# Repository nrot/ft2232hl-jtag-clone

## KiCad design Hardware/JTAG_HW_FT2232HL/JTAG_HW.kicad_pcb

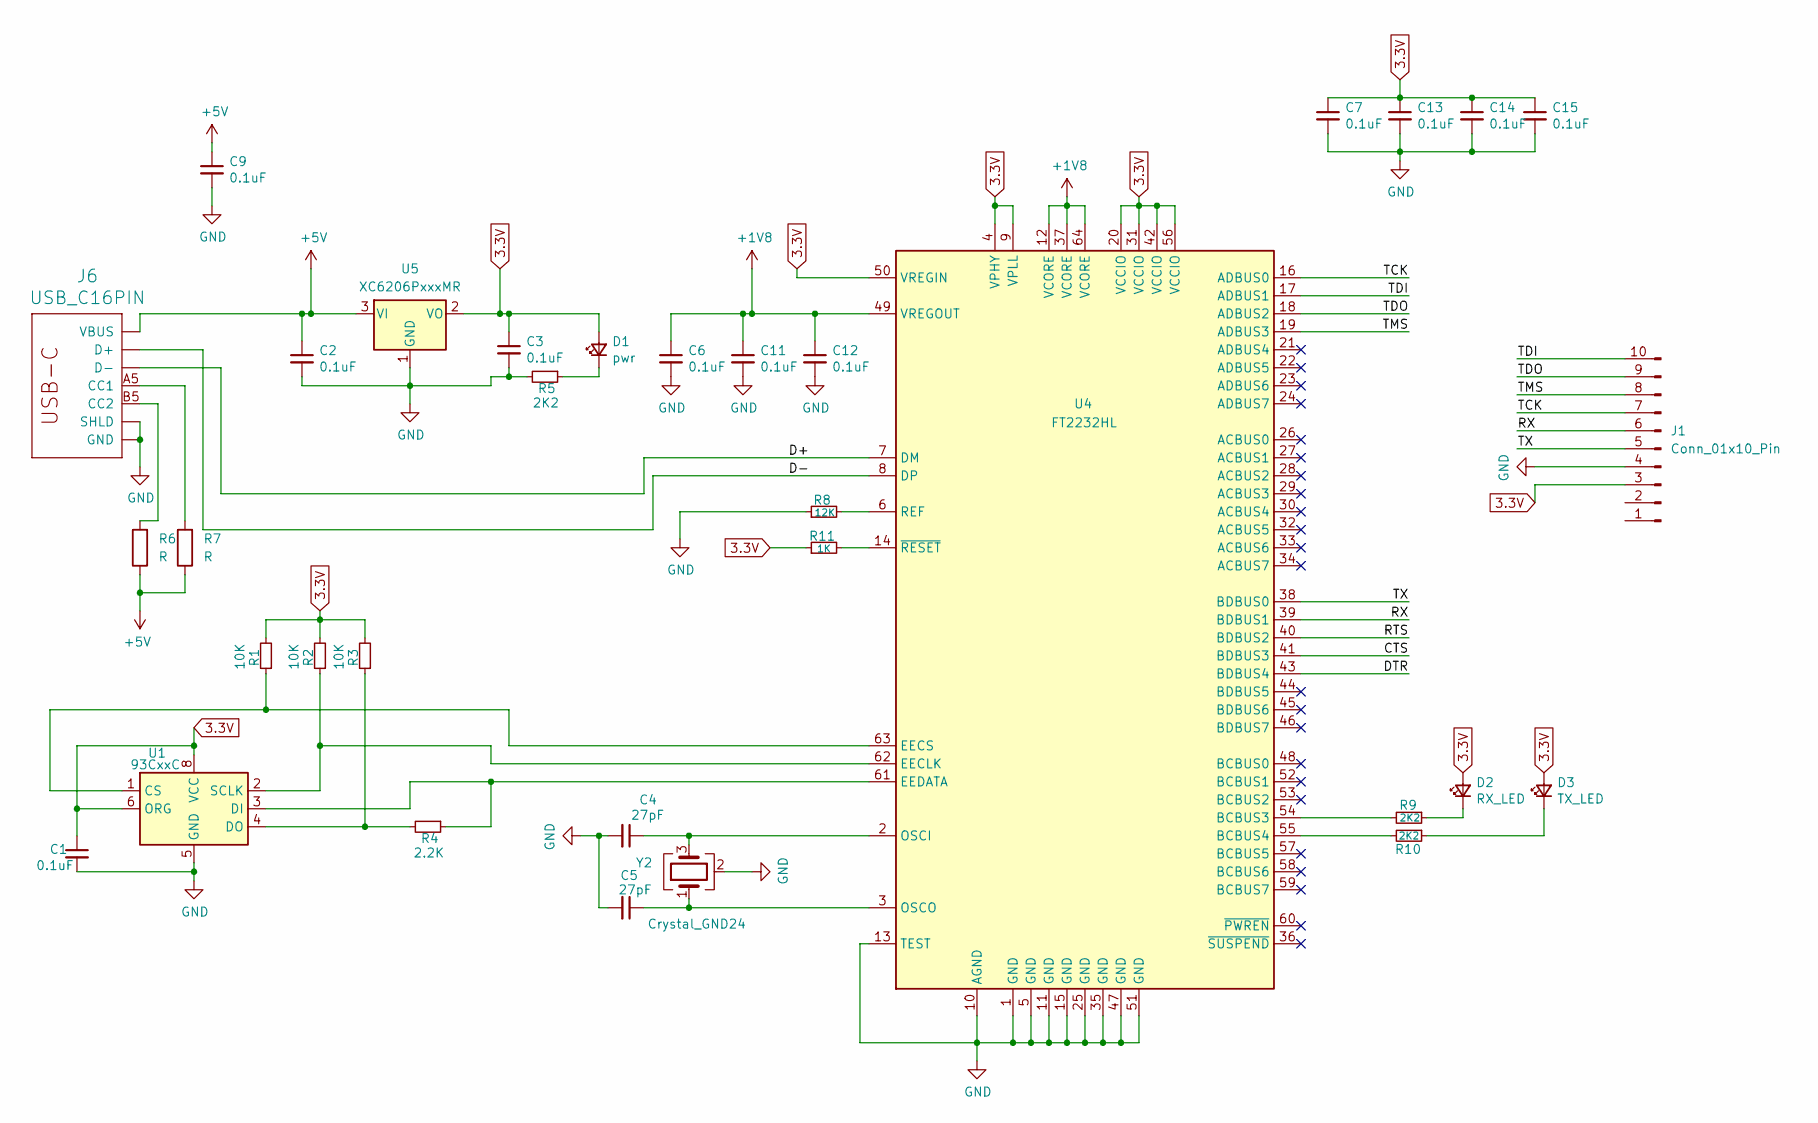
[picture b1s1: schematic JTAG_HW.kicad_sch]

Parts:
C1, C2, C3, C6, C7, C9, C11, C12, C13, C14, C15: 0.1uF; C_0805_2012Metric_Pad1.18x1.45mm_HandSolder
C4, C5: 27pF; C_0805_2012Metric_Pad1.18x1.45mm_HandSolder
D1: pwr; LED_0805_2012Metric_Pad1.15x1.40mm_HandSolder
D2: RX_LED; LED_0805_2012Metric_Pad1.15x1.40mm_HandSolder
D3: TX_LED; LED_0805_2012Metric_Pad1.15x1.40mm_HandSolder
J1: Conn_01x10_Pin; JST_SHL_SM10B-SHLS-TF_1x10-1MP_P1.00mm_Horizontal
J6: USB_C16PIN; USB-C-COM-15111
R1, R2, R3: 10K; R_0805_2012Metric_Pad1.20x1.40mm_HandSolder
R4: 2.2K; R_0805_2012Metric_Pad1.20x1.40mm_HandSolder
R5, R9, R10: 2K2; R_0805_2012Metric_Pad1.20x1.40mm_HandSolder
R6, R7: R
R8: 12K; R_0805_2012Metric_Pad1.20x1.40mm_HandSolder
R11: 1K; R_0805_2012Metric_Pad1.20x1.40mm_HandSolder
U1: 93CxxC; SOIC-8_3.9x4.9mm_P1.27mm
U4: FT2232HL; LQFP-64_10x10mm_P0.5mm
U5: XC6206PxxxMR; SOT-23-3
Y2: Crystal_GND24; Crystal_SMD_3225-4Pin_3.2x2.5mm_HandSoldering

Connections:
3.3V: C1.1, C3.1, C7.1, C13.1, C14.1, C15.1, D1.2 (A), D2.2 (A), D3.2 (A), J1.3, R1.2, R2.2, R3.2, R11.1, U1.6 (ORG), U1.8 (VCC), U4.4 (VPHY), U4.9 (VPLL), U4.20 (VCCIO), U4.31 (VCCIO), U4.42 (VCCIO), U4.50 (VREGIN), U4.56 (VCCIO), U5.2 (VO)
+1V8: C6.1, C11.1, C12.1, U4.12 (VCORE), U4.37 (VCORE), U4.49 (VREGOUT), U4.64 (VCORE)
+5V: C2.1, C9.1, J6.VBUS1 (VBUS), J6.VBUS2 (VBUS), R6.1, R7.1, U5.3 (VI)
/CTS: U4.41 (BDBUS3)
/D+: J6.A7 (D-), J6.B7 (D-), U4.7 (DM)
/D-: J6.A6 (D+), J6.B6 (D+), U4.8 (DP)
/DTR: U4.43 (BDBUS4)
/RTS: U4.40 (BDBUS2)
/RX: J1.6, U4.39 (BDBUS1)
/TCK: J1.7, U4.16 (ADBUS0)
/TDI: J1.10, U4.17 (ADBUS1)
/TDO: J1.9, U4.18 (ADBUS2)
/TMS: J1.8, U4.19 (ADBUS3)
/TX: J1.5, U4.38 (BDBUS0)
GND: C1.2, C2.2, C3.2, C4.2, C5.2, C6.2, C7.2, C9.2, C11.2, C12.2, C13.2, C14.2, C15.2, J1.4, J6.GND, J6.GND2 (GND), J6.SHLD1 (SHLD), J6.SHLD2 (SHLD), J6.SHLD3 (SHLD), J6.SHLD4 (SHLD), J6.SHLD5 (SHLD), J6.SHLD6 (SHLD), J6.SHLD7 (SHLD), J6.SHLD8 (SHLD), R5.2, R8.1, U1.5 (GND), U4.1 (GND), U4.5 (GND), U4.10 (AGND), U4.11 (GND), U4.13 (TEST), U4.15 (GND), U4.25 (GND), U4.35 (GND), U4.47 (GND), U4.51 (GND), U5.1 (GND), Y2.2 (G), Y2.4 (G)
unnamed: D1.1 (K), R5.1
unnamed: D2.1 (K), R9.1
unnamed: D3.1 (K), R10.1
unnamed: J6.A5 (CC1), R7.2
unnamed: J6.B5 (CC2), R6.2
unnamed: R1.1, U1.1 (CS), U4.63 (EECS)
unnamed: R4.1, U1.3 (DI), U4.61 (EEDATA)
unnamed: R3.1, R4.2, U1.4 (DO)
unnamed: R2.1, U1.2 (SCLK), U4.62 (EECLK)
unnamed: R9.2, U4.54 (BCBUS3)
unnamed: R10.2, U4.55 (BCBUS4)
unnamed: C4.1, U4.2 (OSCI), Y2.3
unnamed: C5.1, U4.3 (OSCO), Y2.1
unnamed: R8.2, U4.6 (REF)
unnamed: R11.2, U4.14 (~RESET)

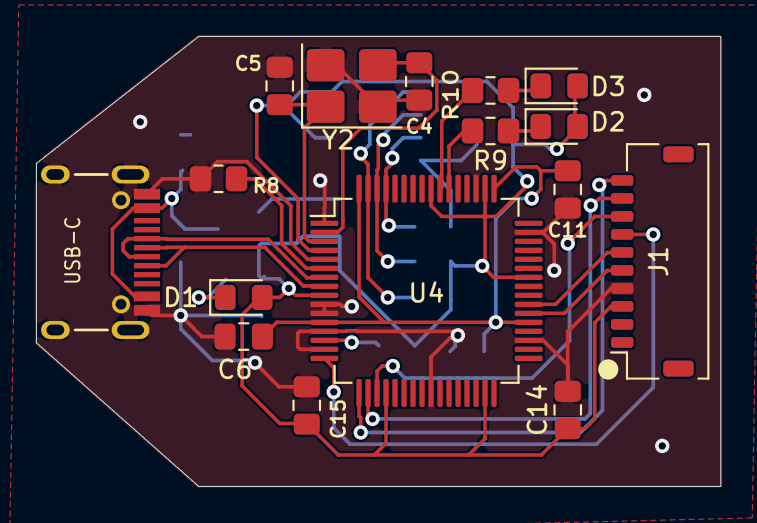
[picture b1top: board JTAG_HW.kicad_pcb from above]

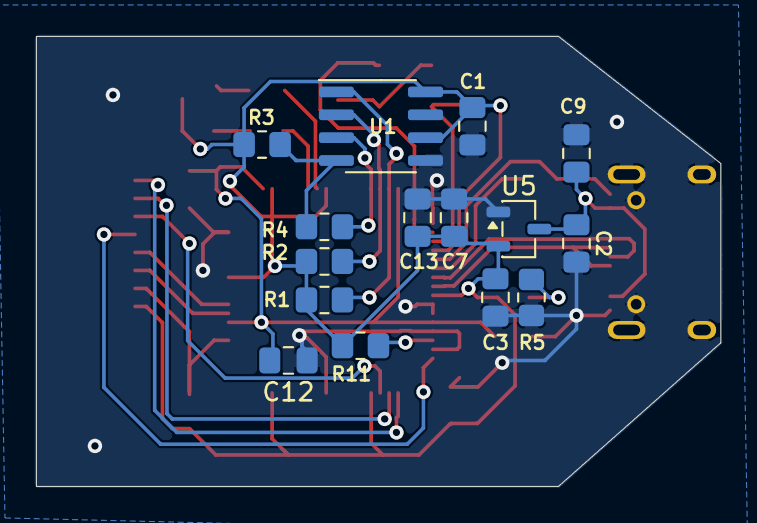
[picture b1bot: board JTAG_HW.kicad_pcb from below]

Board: 2 copper layers, 38.0 x 25.0 mm, 31 parts (15 on the bottom side), 25 nets.
